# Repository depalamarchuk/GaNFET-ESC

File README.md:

# GaNFET-ESC
This is my master project. Work in progress.

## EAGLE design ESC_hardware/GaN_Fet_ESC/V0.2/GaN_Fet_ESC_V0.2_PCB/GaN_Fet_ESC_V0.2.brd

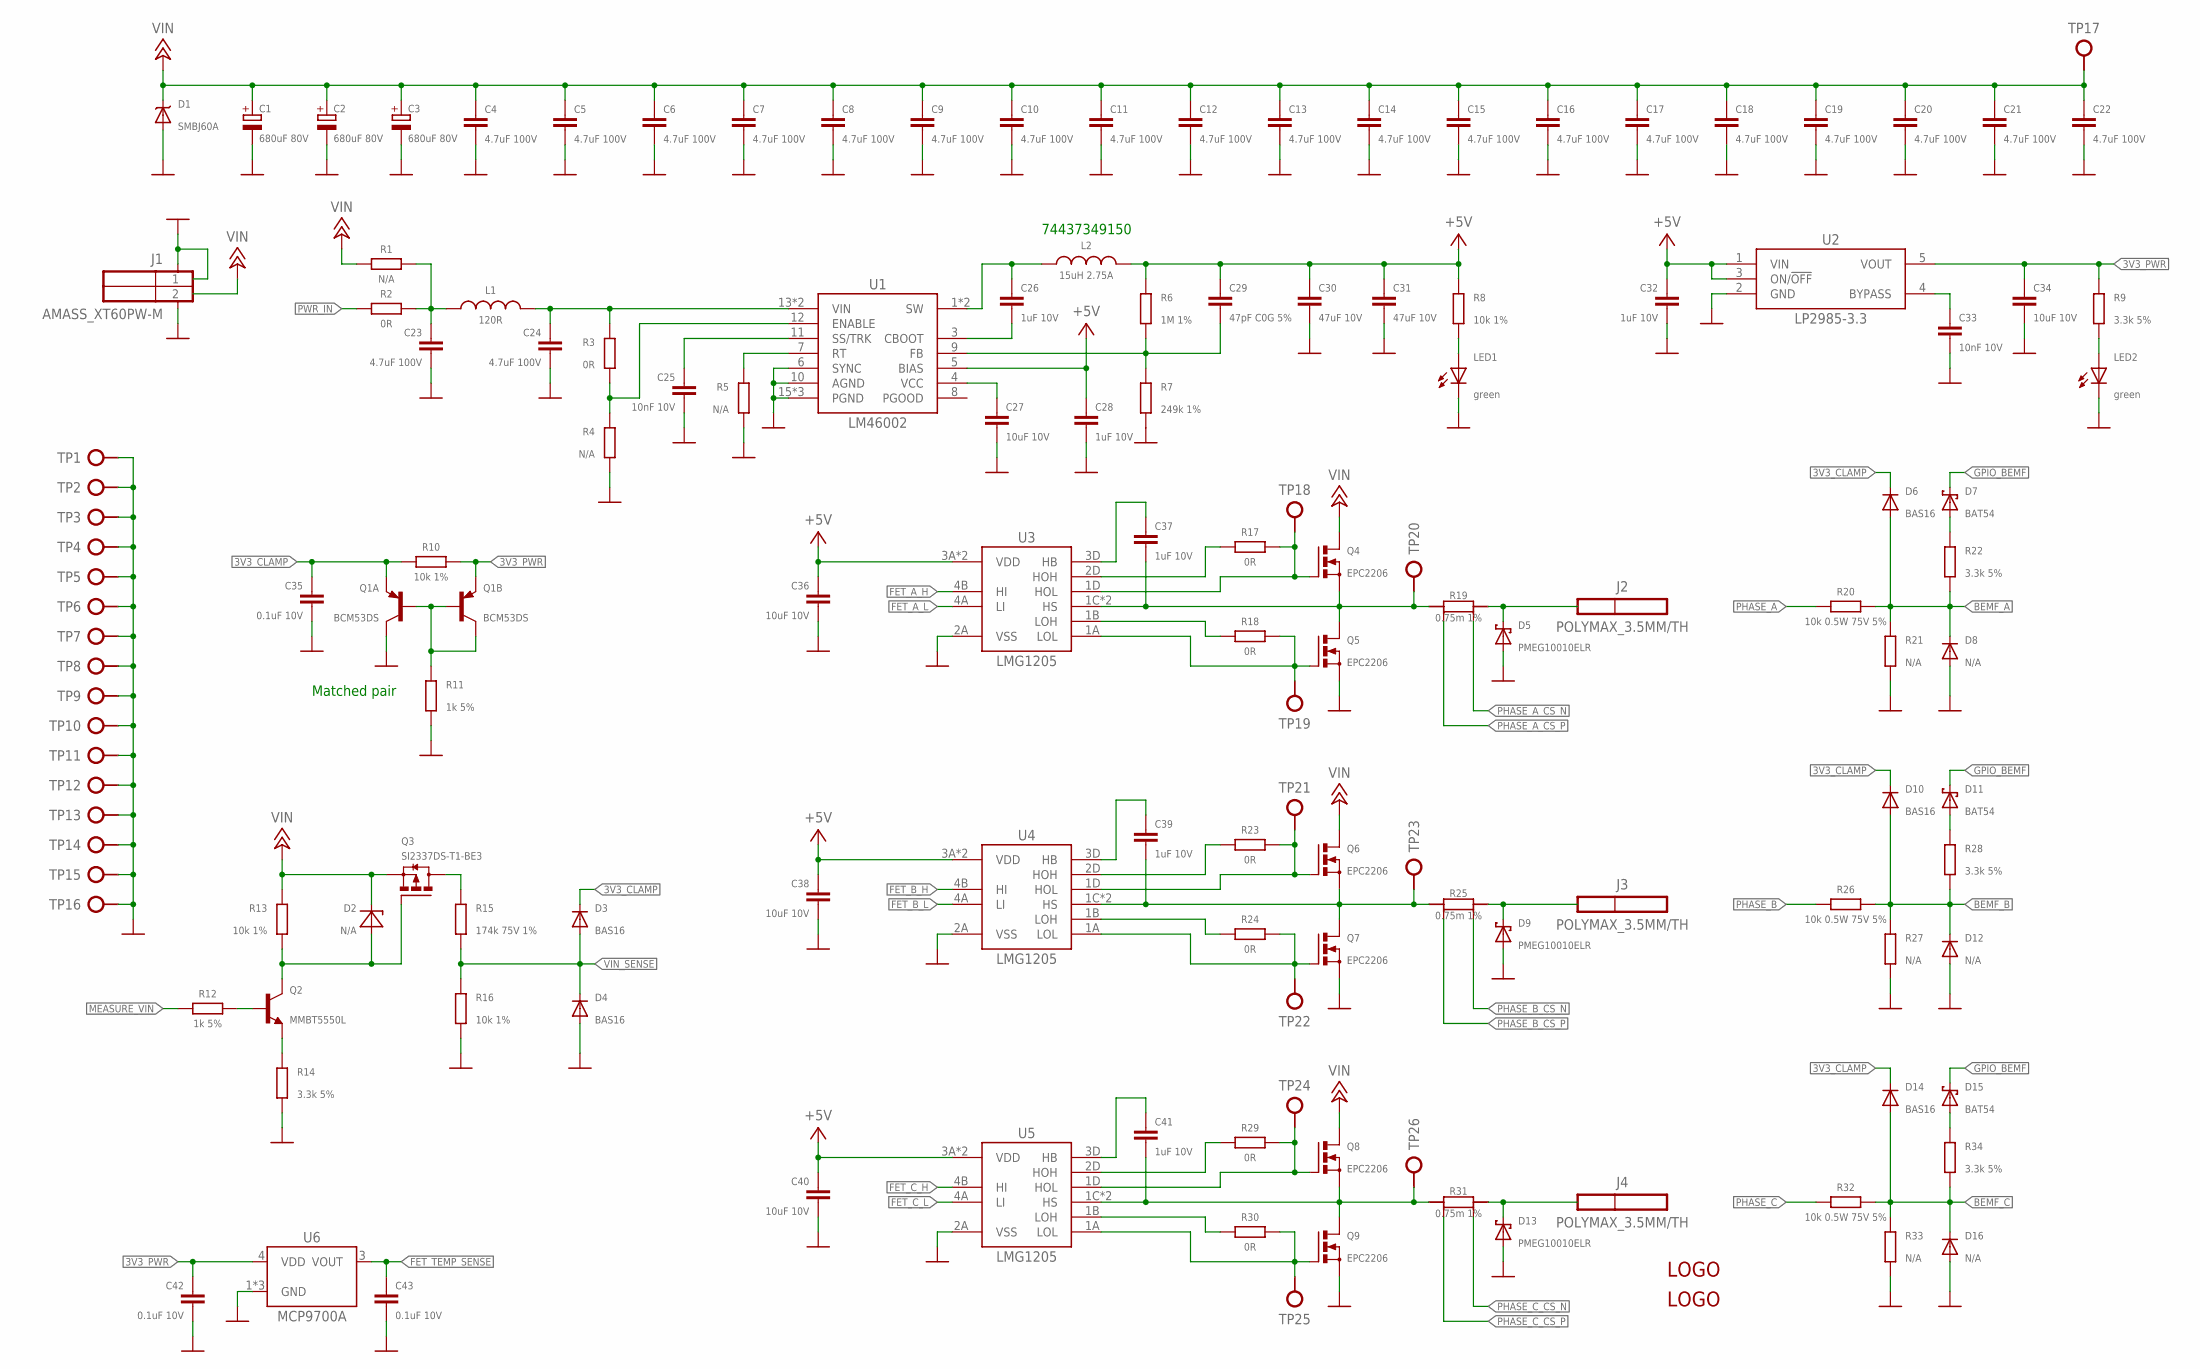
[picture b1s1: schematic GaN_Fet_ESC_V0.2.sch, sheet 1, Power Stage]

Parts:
C1: 680uF 80V; C_7.50_16_26.5_4
C2: 680uF 80V; C_7.50_16_26.5_6
C3: 680uF 80V; C_7.50_16_26.5_5
C4, C5, C6, C7, C8, C9, C10, C11, C12, C13, C14, C15, C16, C17, C18, C19, C20, C21, C22, C23, C24: 4.7uF 100V; C1210
C25, C33: 10nF 10V; C0402
C26, C28, C32, C37, C39, C41: 1uF 10V; C0402
C27, C34, C36, C38, C40: 10uF 10V; C0603
C29: 47pF C0G 5%; C0402
C30, C31: 47uF 10V; C1206
C35, C42, C43: 0.1uF 10V; C0402
D1: SMBJ60A; DO214AA(SMB)
D2: N/A; SOD323F
D3, D4, D6, D10, D14: BAS16; SOD523
D5, D9, D13: PMEG10010ELR; SOD123F
D7, D11, D15: BAT54; SOD523
D8, D12, D16: N/A; SOD523
J1: AMASS_XT60PW-M
J2, J3, J4: POLYMAX_3.5MM/TH; POLYMAX_3.5MM_TH
L1: 120R; L1206
L2: 15uH 2.75A; WURTH_6.6X6.6
LED1, LED2: green; CHIP-LED0603
LOGO1, LOGO2: LOGO
Q1: BCM53DS; SC-74
Q2: MMBT5550L; SOT23
Q3: SI2337DS-T1-BE3; SOT23
Q4, Q5, Q6, Q7, Q8, Q9: EPC2206
R1: N/A; R0603
R2, R3: 0R; R0603
R4, R5, R21, R27, R33: N/A; R0402
R6: 1M 1%; R0402
R7: 249k 1%; R0402
R8, R10, R13, R16: 10k 1%; R0402
R9, R14, R22, R28, R34: 3.3k 5%; R0402
R11, R12: 1k 5%; R0402
R15: 174k 75V 1%; R0603
R17, R18, R23, R24, R29, R30: 0R; R0402
R19, R25, R31: 0.75m 1%; CSS2H-2512
R20, R26, R32: 10k 0.5W 75V 5%; R0805
TP1, TP2, TP3, TP4, TP5, TP6, TP7, TP8, TP9, TP10, TP11, TP12, TP13, TP14, TP15, TP16: TESTPOINT0.5MM; 0.5MM
TP17, TP18, TP19, TP20, TP21, TP22, TP23, TP24, TP25, TP26: TESTPOINT/0.9MM; 0.9MM
U1: LM46002; TSS0P16-PAD
U2: LP2985-3.3; SOT-23-5
U3, U4, U5: LMG1205
U6: MCP9700A; SC-70-5

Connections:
3V3_CLAMP: C35.1, D3.C, D6.C, D10.C, D14.C, Q1.5 (E), R10.1
3V3_PWR: C34.1, C42.1, Q1.4 (E), R9.2, R10.2, U2.5 (VOUT), U6.4 (VDD)
3V3_SINK: Q1.1 (B), Q1.2 (B), Q1.3 (C), R11.2
5V_VCC: C27.1, U1.4 (VCC)
5V_VIN: C24.1, L1.2, R3.2, U1.13 (VIN), U1.14 (VIN)
+5V: C28.1, C29.1, C30.1, C31.1, C32.1, C36.1, C38.1, C40.1, L2.2, R6.2, R8.2, U1.5 (BIAS), U2.1 (VIN), U2.3 (ON/!OFF), U3.3A (VDD), U3.4C (VDD), U4.3A (VDD), U4.4C (VDD), U5.3A (VDD), U5.4C (VDD); also elsewhere on the board
BEMF_A: D6.A, D8.C, R20.2, R21.2, R22.1; also elsewhere on the board
BEMF_B: D10.A, D12.C, R26.2, R27.2, R28.1; also elsewhere on the board
BEMF_C: D14.A, D16.C, R32.2, R33.2, R34.1; also elsewhere on the board
CBOOT: C26.2, U1.3 (CBOOT)
ENABLE: R3.1, R4.2, U1.12 (ENABLE)
FB: C29.2, R6.1, R7.2, U1.9 (FB)
FET_A_H: U3.4B (HI); also elsewhere on the board
FET_A_L: U3.4A (LI); also elsewhere on the board
FET_B_H: U4.4B (HI); also elsewhere on the board
FET_B_L: U4.4A (LI); also elsewhere on the board
FET_C_H: U5.4B (HI); also elsewhere on the board
FET_C_L: U5.4A (LI); also elsewhere on the board
FET_TEMP_SENSE: C43.1, U6.3 (VOUT); also elsewhere on the board
GANFET_A_HB: C37.1, U3.3D (HB)
GANFET_A_HOH: R17.1, U3.2D (HOH)
GANFET_A_HOL: Q4.1 (G), R17.2, TP18.P$1, U3.1D (HOL)
GANFET_A_HS: C37.2, Q4.2 (S), Q4.5 (S), Q4.6 (S), Q4.9 (S), Q4.10 (S), Q4.13 (S), Q4.14 (S), Q4.17 (S), Q4.18 (S), Q4.21 (S), Q4.22 (S), Q4.25 (S), Q4.26 (S), Q4.29 (S), Q4.30 (S), Q5.3 (D), Q5.4 (D), Q5.7 (D), Q5.8 (D), Q5.11 (D), Q5.12 (D), Q5.15 (D), Q5.16 (D), Q5.19 (D), Q5.20 (D), Q5.23 (D), Q5.24 (D), Q5.27 (D), Q5.28 (D), R19.1, R19.3 (1), TP20.P$1, U3.1C (HS), U3.4D (HS)
GANFET_A_LOH: R18.1, U3.1B (LOH)
GANFET_A_LOL: Q5.1 (G), R18.2, TP19.P$1, U3.1A (LOL)
GANFET_B_HB: C39.1, U4.3D (HB)
GANFET_B_HOH: R23.1, U4.2D (HOH)
GANFET_B_HOL: Q6.1 (G), R23.2, TP21.P$1, U4.1D (HOL)
GANFET_B_HS: C39.2, Q6.2 (S), Q6.5 (S), Q6.6 (S), Q6.9 (S), Q6.10 (S), Q6.13 (S), Q6.14 (S), Q6.17 (S), Q6.18 (S), Q6.21 (S), Q6.22 (S), Q6.25 (S), Q6.26 (S), Q6.29 (S), Q6.30 (S), Q7.3 (D), Q7.4 (D), Q7.7 (D), Q7.8 (D), Q7.11 (D), Q7.12 (D), Q7.15 (D), Q7.16 (D), Q7.19 (D), Q7.20 (D), Q7.23 (D), Q7.24 (D), Q7.27 (D), Q7.28 (D), R25.1, R25.3 (1), TP23.P$1, U4.1C (HS), U4.4D (HS)
GANFET_B_LOH: R24.1, U4.1B (LOH)
GANFET_B_LOL: Q7.1 (G), R24.2, TP22.P$1, U4.1A (LOL)
GANFET_C_HB: C41.1, U5.3D (HB)
GANFET_C_HOH: R29.1, U5.2D (HOH)
GANFET_C_HOL: Q8.1 (G), R29.2, TP24.P$1, U5.1D (HOL)
GANFET_C_HS: C41.2, Q8.2 (S), Q8.5 (S), Q8.6 (S), Q8.9 (S), Q8.10 (S), Q8.13 (S), Q8.14 (S), Q8.17 (S), Q8.18 (S), Q8.21 (S), Q8.22 (S), Q8.25 (S), Q8.26 (S), Q8.29 (S), Q8.30 (S), Q9.3 (D), Q9.4 (D), Q9.7 (D), Q9.8 (D), Q9.11 (D), Q9.12 (D), Q9.15 (D), Q9.16 (D), Q9.19 (D), Q9.20 (D), Q9.23 (D), Q9.24 (D), Q9.27 (D), Q9.28 (D), R31.1, R31.3 (1), TP26.P$1, U5.1C (HS), U5.4D (HS)
GANFET_C_LOH: R30.1, U5.1B (LOH)
GANFET_C_LOL: Q9.1 (G), R30.2, TP25.P$1, U5.1A (LOL)
GND: C1.-, C2.-, C3.-, C4.2, C5.2, C6.2, C7.2, C8.2, C9.2, C10.2, C11.2, C12.2, C13.2, C14.2, C15.2, C16.2, C17.2, C18.2, C19.2, C20.2, C21.2, C22.2, C23.2, C24.2, C25.2, C27.2, C28.2, C30.2, C31.2, C32.2, C33.2, C34.2, C35.2, C36.2, C38.2, C40.2, C42.2, C43.2, D1.A, D4.A, D5.A, D8.A, D9.A, D12.A, D13.A, D16.A, J1.1, J1.3, J1.4, LED1.C, LED2.C, Q1.6 (C), Q5.2 (S), Q5.5 (S), Q5.6 (S), Q5.9 (S), Q5.10 (S), Q5.13 (S), Q5.14 (S), Q5.17 (S), Q5.18 (S), Q5.21 (S), Q5.22 (S), Q5.25 (S), Q5.26 (S), Q5.29 (S), Q5.30 (S), Q7.2 (S), Q7.5 (S), Q7.6 (S), Q7.9 (S), Q7.10 (S), Q7.13 (S), Q7.14 (S), Q7.17 (S), Q7.18 (S), Q7.21 (S), Q7.22 (S), Q7.25 (S), Q7.26 (S), Q7.29 (S), Q7.30 (S), Q9.2 (S), Q9.5 (S), Q9.6 (S), Q9.9 (S), Q9.10 (S), Q9.13 (S), Q9.14 (S), Q9.17 (S), Q9.18 (S), Q9.21 (S), Q9.22 (S), Q9.25 (S), Q9.26 (S), Q9.29 (S), Q9.30 (S), R4.1, R5.1, R7.1, R11.1, R14.1, R16.1, R21.1, R27.1, R33.1, TP1.P$1, TP2.P$1, TP3.P$1, TP4.P$1, TP5.P$1, TP6.P$1, TP7.P$1, TP8.P$1, TP9.P$1, TP10.P$1, TP11.P$1, TP12.P$1, TP13.P$1, TP14.P$1, TP15.P$1, TP16.P$1, U1.6 (SYNC), U1.10 (AGND), U1.15 (PGND), U1.16 (PGND), U1.PAD (PGND), U2.2 (GND), U3.2A (VSS), U4.2A (VSS), U5.2A (VSS), U6.1 (GND), U6.2 (GND), U6.5 (GND); also elsewhere on the board
GPIO_BEMF: D7.C, D11.C, D15.C; also elsewhere on the board
LDO_BYPASS: C33.1, U2.4 (BYPASS)
MEASURE_VIN: R12.1; also elsewhere on the board
unnamed: Q2.2 (E), R14.2
unnamed: LED1.A, R8.1
unnamed: D11.A, R28.2
unnamed: D7.A, R22.2
unnamed: D15.A, R34.2
unnamed: LED2.A, R9.1
unnamed: Q2.1 (B), R12.2
unnamed: Q3.3 (D), R15.2
unnamed: C23.1, L1.1, R1.2, R2.2
unnamed: D2.A, Q2.3 (C), Q3.1 (G), R13.1
PHASE_A: D5.C, J2.1, R19.2, R19.4 (2), R20.1
PHASE_A_CS_N: R19.2_SENSE (2K); also elsewhere on the board
PHASE_A_CS_P: R19.1_SENSE (1K); also elsewhere on the board
PHASE_B: D9.C, J3.1, R25.2, R25.4 (2), R26.1
PHASE_B_CS_N: R25.2_SENSE (2K); also elsewhere on the board
PHASE_B_CS_P: R25.1_SENSE (1K); also elsewhere on the board
PHASE_C: D13.C, J4.1, R31.2, R31.4 (2), R32.1
PHASE_C_CS_N: R31.2_SENSE (2K); also elsewhere on the board
PHASE_C_CS_P: R31.1_SENSE (1K); also elsewhere on the board
PWR_IN: R2.1; also elsewhere on the board
RT: R5.2, U1.7 (RT)
SS: C25.1, U1.11 (SS/TRK)
SW: C26.1, L2.1, U1.1 (SW), U1.2 (SW)
VIN: C1.+, C2.+, C3.+, C4.1, C5.1, C6.1, C7.1, C8.1, C9.1, C10.1, C11.1, C12.1, C13.1, C14.1, C15.1, C16.1, C17.1, C18.1, C19.1, C20.1, C21.1, C22.1, D1.K (C), D2.C, J1.2, Q3.2 (S), Q4.3 (D), Q4.4 (D), Q4.7 (D), Q4.8 (D), Q4.11 (D), Q4.12 (D), Q4.15 (D), Q4.16 (D), Q4.19 (D), Q4.20 (D), Q4.23 (D), Q4.24 (D), Q4.27 (D), Q4.28 (D), Q6.3 (D), Q6.4 (D), Q6.7 (D), Q6.8 (D), Q6.11 (D), Q6.12 (D), Q6.15 (D), Q6.16 (D), Q6.19 (D), Q6.20 (D), Q6.23 (D), Q6.24 (D), Q6.27 (D), Q6.28 (D), Q8.3 (D), Q8.4 (D), Q8.7 (D), Q8.8 (D), Q8.11 (D), Q8.12 (D), Q8.15 (D), Q8.16 (D), Q8.19 (D), Q8.20 (D), Q8.23 (D), Q8.24 (D), Q8.27 (D), Q8.28 (D), R1.1, R13.2, TP17.P$1
VIN_SENSE: D3.A, D4.C, R15.1, R16.2; also elsewhere on the board

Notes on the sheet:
74437349150
Matched pair

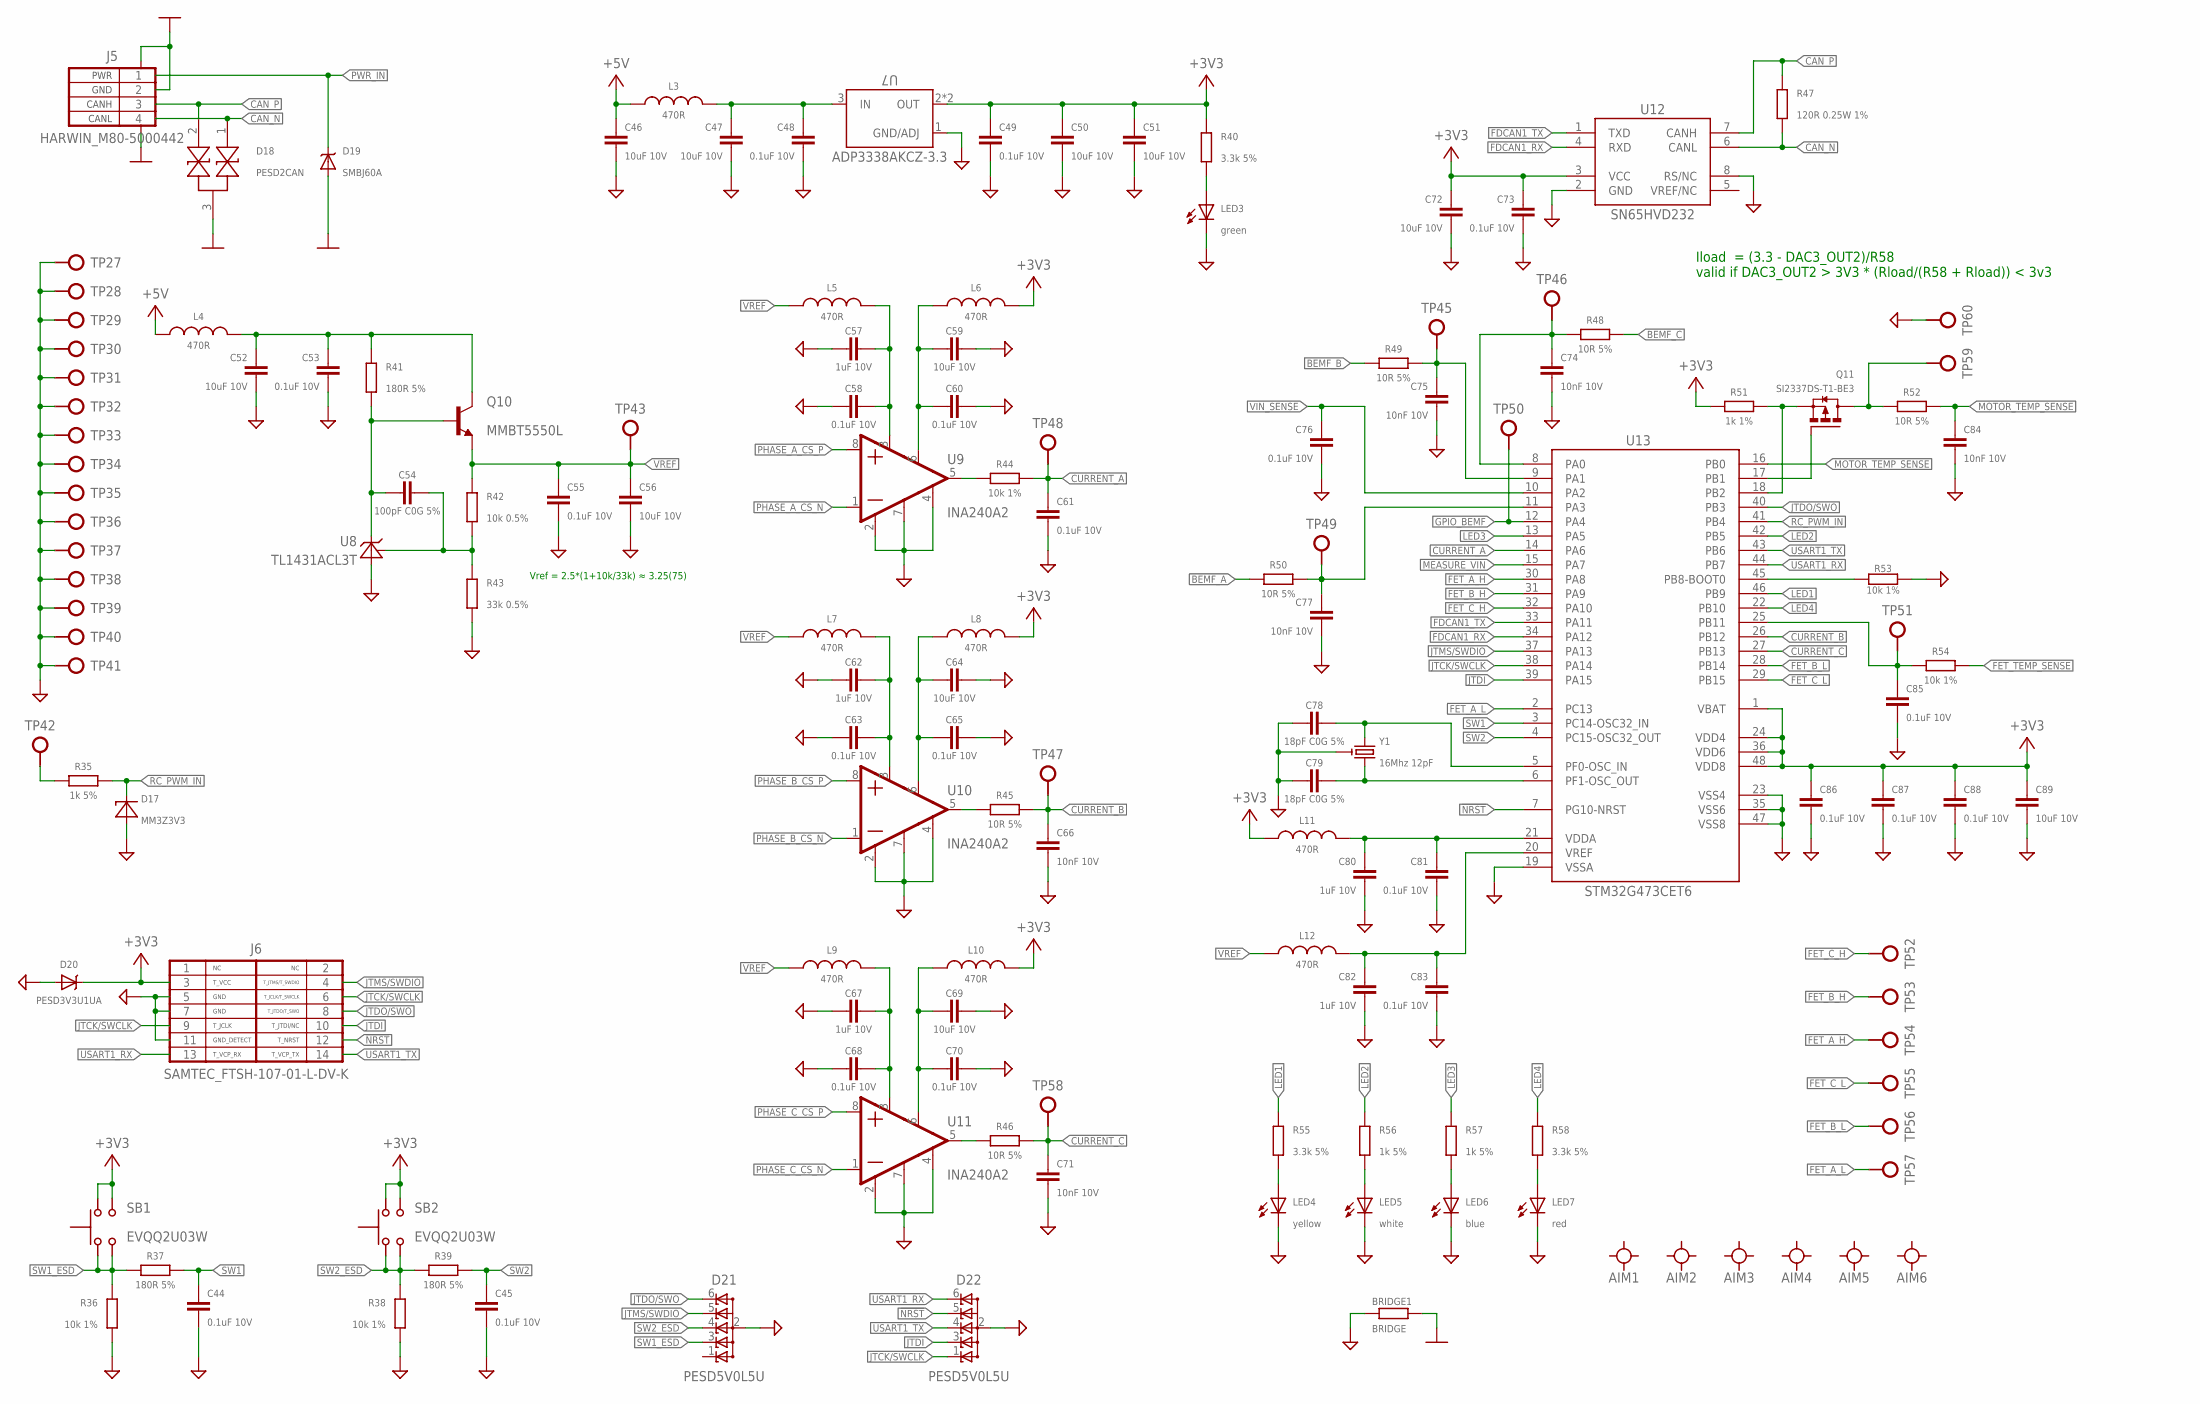
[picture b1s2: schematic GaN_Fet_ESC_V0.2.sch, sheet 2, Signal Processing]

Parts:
AIM1, AIM2, AIM3, AIM4, AIM5, AIM6: AIM_1_MM
BRIDGE1: BRIDGE
C44, C45, C48, C49, C53, C55, C58, C60, C61, C63, C65, C68, C70, C73, C76, C81, C83, C85, C86, C87, C88: 0.1uF 10V; C0402
C46, C47, C50, C51, C52, C56, C59, C64, C69, C72, C89: 10uF 10V; C0603
C54: 100pF C0G 5%; C0402
C57, C62, C67, C80, C82: 1uF 10V; C0402
C66, C71, C74, C75, C77, C84: 10nF 10V; C0402
C78, C79: 18pF C0G 5%; C0402
D17: MM3Z3V3; SOD323F
D18: PESD2CAN; SOT23
D19: SMBJ60A; DO214AA(SMB)
D20: PESD3V3U1UA; SOD323F
D21, D22: PESD5V0L5U; SC-70-6
J5: HARWIN_M80-5000442
J6: SAMTEC_FTSH-107-01-L-DV-K
L3, L4, L5, L6, L7, L8, L9, L10, L11, L12: 470R; L0603
LED3: green; CHIP-LED0603
LED4: yellow; CHIP-LED0603
LED5: white; CHIP-LED0603
LED6: blue; CHIP-LED0603
LED7: red; CHIP-LED0603
Q10: MMBT5550L; SOT23
Q11: SI2337DS-T1-BE3; SOT23
R35, R56, R57: 1k 5%; R0402
R36, R38, R44, R53, R54: 10k 1%; R0402
R37, R39, R41: 180R 5%; R0402
R40, R55, R58: 3.3k 5%; R0402
R42: 10k 0.5%; R0603
R43: 33k 0.5%; R0603
R45, R46, R48, R49, R50, R52: 10R 5%; R0402
R47: 120R 0.25W 1%; R0805
R51: 1k 1%; R0402
SB1, SB2: EVQQ2U03W
TP27, TP28, TP29, TP30, TP31, TP32, TP33, TP34, TP35, TP36, TP37, TP38, TP39, TP40: TESTPOINT0.5MM; 0.5MM
TP41, TP42, TP43, TP45, TP46, TP47, TP48, TP49, TP50, TP51, TP52, TP53, TP54, TP55, TP56, TP57, TP58, TP59, TP60: TESTPOINT/0.9MM; 0.9MM
U7: ADP3338AKCZ-3.3; SOT223
U8: TL1431ACL3T; SOT23
U9, U10, U11: INA240A2; SOIC-8
U12: SN65HVD232; SOIC-8
U13: STM32G473CET6; LQFP-48
Y1: 16Mhz 12pF; CRYSTAL_SMD_3.2X2.5MM

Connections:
!NRST: D22.5, J6.12, U13.7 (PG10-NRST)
+3V3: C49.1, C50.1, C51.1, C72.1, C73.1, C86.1, C87.1, C88.1, C89.1, D20.C, J6.3, L6.1, L8.1, L10.1, L11.1, R40.2, R51.2, SB1.2 (B1), SB1.2' (B2), SB2.2 (B1), SB2.2' (B2), U7.2 (OUT), U7.4 (OUT), U12.3 (VCC), U13.1 (VBAT), U13.24 (VDD4), U13.36 (VDD6), U13.48 (VDD8)
+5V: C46.1, L3.2, L4.2; also elsewhere on the board
BEMF_A: R50.1; also elsewhere on the board
BEMF_A_FILT: C77.1, R50.2, TP49.P$1, U13.11 (PA3)
BEMF_B: R49.1; also elsewhere on the board
BEMF_B_FILT: C75.1, R49.2, TP45.P$1, U13.9 (PA1)
BEMF_C: R48.1; also elsewhere on the board
BEMF_C_FILT: C74.1, R48.2, TP46.P$1, U13.8 (PA0)
BOOT0: R53.2, U13.45 (PB8-BOOT0)
CAN_N: D18.1, J5.4, R47.1, U12.6 (CANL)
CAN_P: D18.2, J5.3, R47.2, U12.7 (CANH)
CS_A: R44.1, U9.5 (OUT)
CS_A_VCC: C59.1, C60.1, L6.2, U9.6 (VS)
CS_B: R45.1, U10.5 (OUT)
CS_B_VCC: C64.1, C65.1, L8.2, U10.6 (VS)
CS_C: R46.2, U11.5 (OUT)
CS_C_VCC: C69.1, C70.1, L10.2, U11.6 (VS)
CURRENT_A: C61.1, R44.2, TP48.P$1, U13.14 (PA6)
CURRENT_B: C66.1, R45.2, TP47.P$1, U13.26 (PB12)
CURRENT_C: C71.1, R46.1, TP58.P$1, U13.27 (PB13)
CURRENT_SOURCE: Q11.3 (D), R52.1, TP59.P$1
FDCAN1_RX: U12.4 (RXD), U13.34 (PA12)
FDCAN1_TX: U12.1 (TXD), U13.33 (PA11)
FET_A_H: TP54.P$1, U13.30 (PA8); also elsewhere on the board
FET_A_L: TP57.P$1, U13.2 (PC13); also elsewhere on the board
FET_B_H: TP53.P$1, U13.31 (PA9); also elsewhere on the board
FET_B_L: TP56.P$1, U13.28 (PB14); also elsewhere on the board
FET_C_H: TP52.P$1, U13.32 (PA10); also elsewhere on the board
FET_C_L: TP55.P$1, U13.29 (PB15); also elsewhere on the board
FET_TEMP_SENSE: R54.1; also elsewhere on the board
FET_TEMP_SENSE_FILT: C85.1, R54.2, TP51.P$1, U13.25 (PB11)
GND: BRIDGE1.2, D18.3, D19.A, J5.2, J5.5, J5.6, J5.7, J5.8; also elsewhere on the board
GND1: BRIDGE1.1, C44.2, C45.2, C46.2, C47.2, C48.2, C49.2, C50.2, C51.2, C52.2, C53.2, C55.2, C56.2, C57.2, C58.2, C59.2, C60.2, C61.2, C62.2, C63.2, C64.2, C65.2, C66.2, C67.2, C68.2, C69.2, C70.2, C71.2, C72.2, C73.2, C74.2, C75.2, C76.2, C77.2, C78.1, C79.1, C80.2, C81.2, C82.2, C83.2, C84.2, C85.2, C86.2, C87.2, C88.2, C89.2, D17.A, D20.A, D21.2, D22.2, J6.5, J6.7, J6.11, LED3.C, LED4.C, LED5.C, LED6.C, LED7.C, R36.1, R38.1, R43.1, R53.1, TP27.P$1, TP28.P$1, TP29.P$1, TP30.P$1, TP31.P$1, TP32.P$1, TP33.P$1, TP34.P$1, TP35.P$1, TP36.P$1, TP37.P$1, TP38.P$1, TP39.P$1, TP40.P$1, TP41.P$1, TP60.P$1, U7.1 (GND/ADJ), U8.3 (A), U9.2 (GND), U9.4 (NC), U9.7 (REF1), U10.2 (GND), U10.4 (NC), U10.7 (REF1), U11.2 (GND), U11.4 (NC), U11.7 (REF1), U12.2 (GND), U12.8 (RS/NC), U13.19 (VSSA), U13.23 (VSS4), U13.35 (VSS6), U13.47 (VSS8), Y1.2 (3), Y1.4 (3)
GPIO_BEMF: TP50.P$1, U13.12 (PA4); also elsewhere on the board
JTCK/SWCLK: D22.1, J6.6, J6.9, U13.38 (PA14)
JTDI: D22.3, J6.10, U13.39 (PA15)
JTDO/SWO: D21.6, J6.8, U13.40 (PB3)
JTMS/SWDIO: D21.5, J6.4, U13.37 (PA13)
LED1: R55.2, U13.46 (PB9)
LED2: R56.2, U13.42 (PB5)
LED3: R57.2, U13.13 (PA5)
LED4: R58.2, U13.22 (PB10)
MCU_VDDA: C80.1, C81.1, L11.2, U13.21 (VDDA)
MCU_VEF: C82.1, C83.1, L12.2, U13.20 (VREF)
MEASURE_VIN: U13.15 (PA7); also elsewhere on the board
MOTOR_TEMP_SENSE: C84.1, R52.2, U13.16 (PB0)
unnamed: LED4.A, R55.1
unnamed: R35.2, TP42.P$1
unnamed: LED3.A, R40.1
unnamed: LED6.A, R57.1
unnamed: LED7.A, R58.1
unnamed: C54.1, Q10.1 (B), R41.1, U8.1 (C)
unnamed: C78.2, U13.5 (PF0-OSC_IN), Y1.1
unnamed: C79.2, U13.6 (PF1-OSC_OUT), Y1.3 (2)
unnamed: C52.1, C53.1, L4.1, Q10.3 (C), R41.2
unnamed: C47.1, C48.1, L3.1, U7.3 (IN)
unnamed: LED5.A, R56.1
OPAMP3_VINM: Q11.2 (S), R51.1, U13.18 (PB2)
OPAMP3_VOUT: Q11.1 (G), U13.17 (PB1)
PHASE_A_CS_N: U9.1 (IN-); also elsewhere on the board
PHASE_A_CS_P: U9.8 (IN+); also elsewhere on the board
PHASE_B_CS_N: U10.1 (IN-); also elsewhere on the board
PHASE_B_CS_P: U10.8 (IN+); also elsewhere on the board
PHASE_C_CS_N: U11.1 (IN-); also elsewhere on the board
PHASE_C_CS_P: U11.8 (IN+); also elsewhere on the board
PWR_IN: D19.K (C), J5.1; also elsewhere on the board
RC_PWM_IN: D17.C, R35.1, U13.41 (PB4)
SW1: C44.1, R37.1, U13.3 (PC14-OSC32_IN)
SW1_ESD: D21.3, R36.2, R37.2, SB1.1 (A1), SB1.1' (A2)
SW2: C45.1, R39.1, U13.4 (PC15-OSC32_OUT)
SW2_ESD: D21.4, R38.2, R39.2, SB2.1 (A1), SB2.1' (A2)
TL431_REF: C54.2, R42.1, R43.2, U8.2 (REF)
USART1_RX: D22.6, J6.13, U13.44 (PB7)
USART1_TX: D22.4, J6.14, U13.43 (PB6)
VIN_SENSE: C76.1, U13.10 (PA2); also elsewhere on the board
VREF: C55.1, C56.1, L5.2, L7.2, L9.2, L12.1, Q10.2 (E), R42.2, TP43.P$1
VREF_A: C57.1, C58.1, L5.1, U9.3 (REF2)
VREF_B: C62.1, C63.1, L7.1, U10.3 (REF2)
VREF_C: C67.1, C68.1, L9.1, U11.3 (REF2)

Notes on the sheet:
T_NRST
GND_DETECT
T_VCC
T_JTMS/T_SWDIO
T_JCLK/T_SWCLK
T_JTDO/T_SWO
GND
T_VCP_TX
T_VCP_RX
T_JCLK
T_JTDI/NC
Vref = 2.5*(1+10k/33k) ≈ 3.25(75)
Iload = (3.3 - DAC3_OUT2)/R58 valid if DAC3_OUT2 > 3V3 * (Rload/(R58 + Rload)) < 3v3
PWR
CANH
CANL

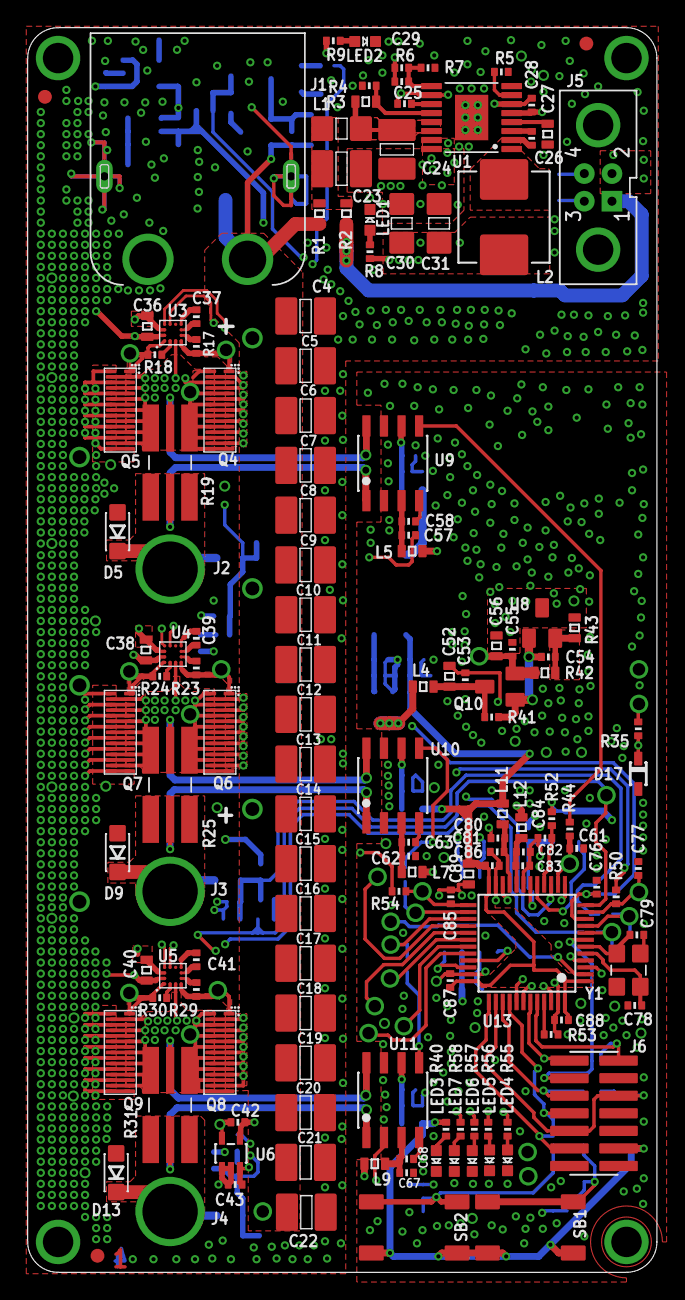
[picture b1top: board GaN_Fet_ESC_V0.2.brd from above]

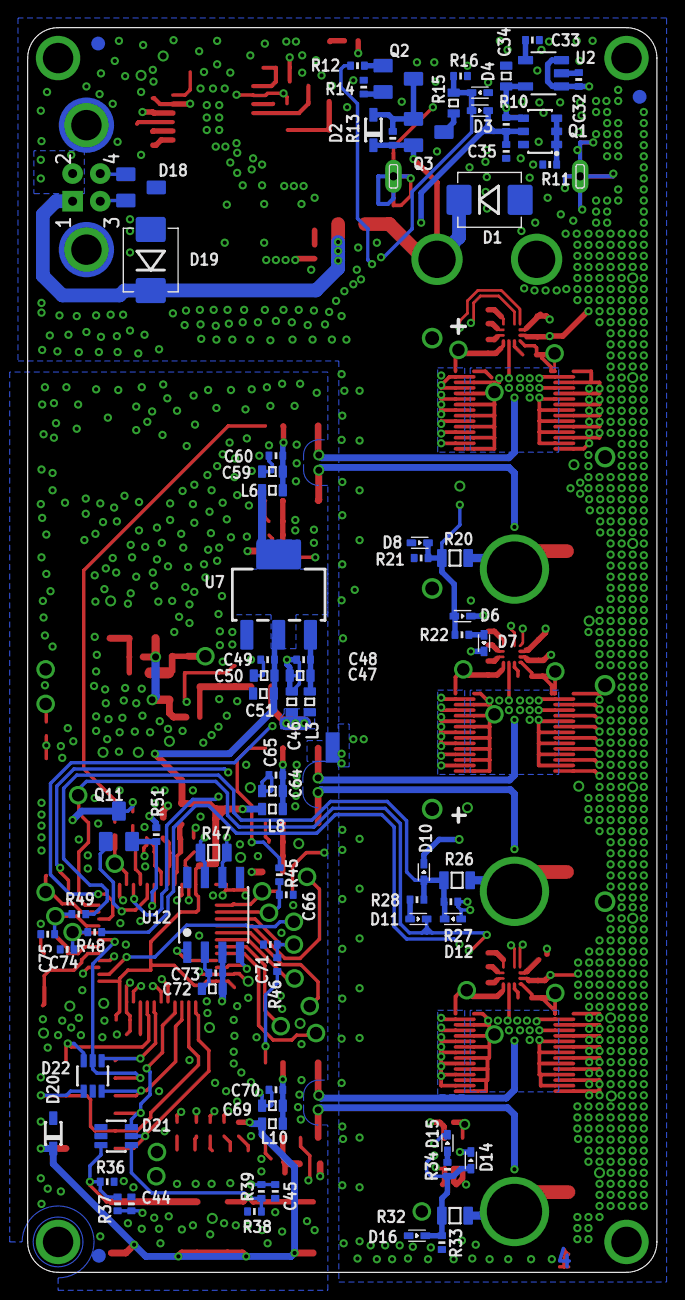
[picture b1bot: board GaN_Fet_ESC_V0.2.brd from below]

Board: 4 copper layers, 45.5 x 90.0 mm, 289 parts (87 on the bottom side), 124 nets.

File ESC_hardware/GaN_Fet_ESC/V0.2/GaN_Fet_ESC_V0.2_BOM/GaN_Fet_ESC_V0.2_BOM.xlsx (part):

|  | GaN Fet Electronic Speed Controller PCB BOM
Qty | Parts | Value | Description | Case | Supplier | Supplier ID | Manufacturer | Manufacturer ID | Alternative manufacturers. 1 – All 2 – First ask 3 – do not replace
2 | C78, C79 | 18pF C0G 5% | ±5% ≥6.3V Ceramic Capacitor C0G/NP0 | C0402 | Mouser | 80-C0402C180J8G | KEMET | C0402C180J8GACTU | 1
1 | C29 | 47pF C0G 5% | ±5% ≥10V Ceramic Capacitor C0G/NP0 | C0402 | Mouser | 80-C0402C470J5G | KEMET | C0402C470J5GACTU | 1
1 | C54 | 100pF C0G 5% | ±5% ≥6.3V Ceramic Capacitor C0G/NP0 | C0402 | Mouser | 80-C0402C101J5G7411 | KEMET | C0402C101J5GAC7411 | 1
8 | C25, C33, C61, C66, C71, C80, C82, C83 | 10nF 10V | ±10% ≥10V Ceramic Capacitor X7R | C0402 | Mouser | 80-C0402C103K3R | KEMET | C0402C103K3RACTU | 1
23 | C35, C42, C43, C44, C45, C48, C49, C53, C55, C58, C60, C63, C65, C68, C70, C73,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 | 0.1uF 10V | ±10% ≥10V Ceramic Capacitor X7R | C0402 | Mouser | 81-GRM155R71H104KE4D | Murata Electronics | GRM155R71H104KE14D | 1
11 | C27, C28, C32, C37, C39, C41, C57, C62, C67, C74, C76 | 1uF 10V | ±10% ≥10V Ceramic Capacitor X7S | C0402 | Mouser | 81-GCM155C71A105KE8D | Murata Electronics | GCM155C71A105KE38D | 1
16 | C26, C34, C36, C38, C40, C46, C47, C50, C51, C52, C56, C59, C64, C69, C72, C87 | 10uF 10V | ±10% ≥10V Ceramic Capacitor X7T | C0603 | Mouser | 81-GRM188D71A106KA3 | Murata Electronics | GRM188D71A106KA73D | 1
21 | C4, C5, C6, C7, C8, C9, C10, C11, C12, C13, C14, C15, C16, C17, C18, C19, C20, 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 | 4.7uF 100V | ±10% ≥100V Ceramic Capacitor X7S | C1210 | Mouser | 963-HMK325C7475KM-PE | Taiyo Yuden | HMK325C7475KM-PE | 1
2 | C30, C31 | 47uF 10V | ±10% ≥10V Ceramic Capacitor X5R | C1206 | Mouser | 81-GRM31CR61A476KE5L | Murata Electronics | GRM31CR61A476KE15L | 1
3 | C1, C2, C3 | 680uF 80V | 680µF 80V Aluminum Electrolytic Capacitors Radial, Can 10000 Hrs @ 105°C | C_7.50_16_26.5 | Mouser | 661-EKZN800E681ML25S | United Chemi-Con | EKZN800ELL681ML25S | 2
6 | R17, R18, R23, R24, R29, R30 | 0R | ±5% 100 mW 50V Chip Resistor 0402 | R0402 | Mouser | 660-RK73Z1ETTP | KOA Speer | RK73Z1ETTP | 1
2 | R2, R3 | 0R | ±5% 100 mW 50V Chip Resistor 0402 | R0603 | Mouser | 667-ERJ-U030R00V | Panasonic | ERJ-U030R00V | 1
3 | R19, R25, R31 | 0.75m 1% | Current Sense Resistors - SMD 3W 0.0007 Ohm 1% | CSS2H-2512 | Mouser | 756-LRMAP25R00075FT4 | Welwyn Components / TT Electronics | LRMAP2512-R00075FT4 | 1
6 | R44, R45, R46, R48, R49, R50 | 10R 5% | ±5% 62.5 mW 50V Chip Resistor 0402 | R0402 | Mouser | 603-RC0402JR-0710RL | YAGEO | RC0402JR-0710RL | 1
1 | R47 | 120R 0.25W 1% | ±1% 250 mW Chip Resistor 0805 | R0805 | Mouser | 667-ERJ-P06F1200V | Panasonic | ERJ-P06F1200V | 1
3 | R37, R39, R41 | 180R 5% | ±5% 62.5 mW 50V Chip Resistor 0402 | R0402 | Mouser | 667-ERJ-2RKF1800X | Panasonic | ERJ-2RKF1800X | 1
5 | R11, R12, R35, R55, R56 | 1k 5% | ±5% 62.5 mW 50V Chip Resistor 0402 | R0402 | Mouser | 603-AC0402JR-071KL | YAGEO | AC0402JR-071KL | 1
9 | R9, R14, R22, R28, R34, R40, R53, R54, R57 | 3.3k 5% | ±5% 62.5 mW 50V Chip Resistor 0402 | R0402 | Mouser | 603-AC0402JR-073K3L | YAGEO | AC0402JR-073K3L | 1
1 | R42 | 10k 0.5% | ±0.5% 25ppm 62.5 mW 50V Chip Resistor 0603 | R0603 | Mouser | 279-CPF0603D10KE | TE Connectivity / Holsworthy | CPF0603D10KE | 1
8 | R8, R10, R13, R16, R36, R38, R51, R52 | 10k 1% | ±1% 62.5 mW 50V Chip Resistor 0402 | R0402 | Mouser | 603-RC0402FR-0710KP | YAGEO | RC0402FR-0710KP | 1
3 | R20, R26, R32 | 10k 0.5W 75V 5% | ±5% 500 mW Chip Resistor 0805 | R0805 | Mouser | 667-ERJ-P06J103V | Panasonic | ERJ-P06J103V | 1
1 | R43 | 33k 0.5% | ±0.5% 25ppm 62.5 mW 50V Chip Resistor 0603 | R0603 | Mouser | 667-ERA-3AED333V | Panasonic | ERA-3AED333V | 1
1 | R15 | 174k 75V 1% | ±1% 62.5 mW 50V Chip Resistor 0603 | R0603 | Mouser | 603-AC0603FR-07174KL | YAGEO | AC0603FR-07174KL | 1
1 | R7 | 249k 1% | ±1% 62.5 mW 50V Chip Resistor 0402, AEC-Q200 | R0402 | Mouser | 660-RK73H1ETTP2493F | KOA Speer | RK73H1ETTP2493F | 1
1 | R6 | 1M 1% | ±1% 62.5 mW 50V Chip Resistor 0402, AEC-Q200 | R0402 | Mouser | 660-RK73H1ETTP1004F | KOA Speer | RK73H1ETTP1004F | 1
1 | L1 | 120R | Ferrite Beads 1206 120ohms ≥3A | L1206 | Mouser | 81-BLM31KN121SZ1L | Murata Electronics | BLM31KN121SZ1L | 1
10 | L3, L4, L5, L6, L7, L8, L9, L10, L11, L12 | 470R | Ferrite Beads 0603 470ohms | L0603 | Mouser | 81-BLM18KG471SN1D | Murata Electronics | BLM18KG471SN1D | 1
1 | L2 | 15uH 2.75A | Fixed Inductors WE-LHMI Powr SMD7050 15uH 2.75A 92mOhm | WURTH_6.6X6.6 | Mouser | 710-74437349150 | Wurth Elektronik | 74437349150 | 3
1 | Y1 | 16Mhz 12pF | Crystals AEC-Q200 16MHz 12pF 3.2x2.5mm | CRYSTAL_SMD_3.2X2.5MM | Mouser | 581-CX3225SB16000HLJ | Kyocera AVX | CX3225SB16000H0FLJCC | 1
2 | D1, D21 | SMBJ60A | ESD Suppressors / TVS Diodes 60volts 5uA 6.2 Amps Uni-Dir | DO214AA(SMB) | Mouser | 652-SMBJ60A | Bourns | SMBJ60A | 1
1 | D2 | MM3Z12V | Zener Diodes 12V 200mW | SOD323F | Mouser | 863-MM3Z12VT1G | onsemi | MM3Z12VT1G | 1
5 | D3, D4, D7, D12, D17 | BAS16 | Diodes - General Purpose, Power, Switching SWITCHING DIODE | SOD523 | Mouser | 863-BAS16XV2T5G | onsemi | BAS16XV2T5G | 1
3 | D5, D10, D15 | PMEG10010ELR | Schottky Diodes & Rectifiers 1A Schottky Barrier Rectifier | SOD123F | Mouser | 771-PMEG10010ELRX | Nexperia | PMEG10010ELRX | 1
3 | D8, D13, D18 | BAT54 | Schottky Diodes & Rectifiers 30V 200mW Single | SOD523 | Mouser | 863-BAT54XV2T1G | onsemi | BAT54XV2T1G | 1
1 | D20 | PESD2CAN | ESD Suppressors / TVS Diodes DIODE ESD PROT | SOT23 | Mouser | 771-PESD2CANFD24V-TR | Nexperia | PESD2CANFD24V-TR | 1
1 | D22 | MM3Z3V3 | Zener Diodes 3.3V 200mW | SOD323F | Mouser | 863-MM3Z3V3T1G | onsemi | MM3Z3V3T1G | 1
1 | D23 | PESD3V3U1UA | ESD Suppressors / TVS Diodes DIODE ARRAY ESD 1L ULTRA LO CD | SOD323F | Mouser | 771-PESD3V3U1UA-T/R | Nexperia | PESD3V3U1UA,115 | 1
2 | D24, D25 | PESD5V0L5U | ESD Suppressors / TVS Diodes Diode TVS Quint Uni-Dir 5V 25W 6-Pin | SC-70-6 | Mouser | 771-PESD5V0L5UY,125 | Nexperia | PESD5V0L5UY,125 | 1
4 | LED1, LED2, LED3, LED4 | green | Green 570nm LED Indication - Discrete 2V 0603 (1608 Metric) | CHIP-LED0603 | Mouser | 710-150060VS75000 | Wurth Elektronik | 150060VS75000 | 1
1 | LED5 | yellow | Yellow 589nm LED Indication - Discrete 2V 0603 (1608 Metric) | CHIP-LED0603 | Mouser | 710-150060YS75000 | Wurth Elektronik | 150060YS75000 | 1
1 | LED6 | white | Standard LEDs - SMD White Clear Non-Diff | CHIP-LED0603 | Mouser | 78-VLMW1300-GS08 | Vishay Semiconductors | VLMW1300-GS08 | 1
1 | LED7 | blue | Blue 470nm LED Indication - Discrete 3.2V 0603 (1608 Metric) | CHIP-LED0603 | Mouser | 710-150060BS75000 | Wurth Elektronik | 150060BS75000 | 1
1 | LED8 | red | Red 625nm LED Indication - Discrete 2V 0603 (1608 Metric) | CHIP-LED0603 | Mouser | 710-150060RS75000 | Wurth Elektronik | 150060RS75000 | 1
1 | Q1 | BCM53DS | Bipolar Transistors - BJT BCM53DS SC-74 | SC-74 | Mouser | 771-BCM53DSX | Nexperia | BCM53DSX | 2
2 | Q2, Q10 | MMBT5550L | Bipolar Transistors - BJT SS HV XSTR NPN 160V | SOT23 | Mouser | 863-MMBT5550LT1G | onsemi | MMBT5550LT1G | 1
1 | Q3 | SI2337DS-T1-BE3 | MOSFET P-CHANNEL 80-V (D-S) | SOT23C | Mouser | SI2337DS-T1-BE3 | Vishay / Siliconix | SI2337DS-T1-BE3 | 1
6 | Q4, Q5, Q6, Q7, Q8, Q9 | EPC2206 | GaN FET, eGaN®, Vds = 80V, Rds(on) = 2.2 mOhm, Id = 90 A, Qgd = 3 nC, Qrr = 0 n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 | EPC2206 | Digi-Key | 917-1212-1-ND | EPC | EPC2206 | 2
1 | U1 | LM46002 | 3.5-V to 60-V, 2-A Synchronous Step-Down Voltage Converter | TSS0P16-PAD | Mouser | 595-LM46002PWPR | Texas Instruments | LM46002PWPR | 3
1 | U2 | LP2985-3.3 | LP2985 150-mA Low-noise Low-dropout Regulator With Shutdown | SOT-23-5 | Mouser | 595-LP2985-33DBVR | Texas Instruments | LP2985-33DBVR | 2
3 | U3, U4, U5 | LMG1205 | LMG120580-V, 1.2-A to 5-A, Half Bridge GaN Driver with Integrated Bootstrap Dio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 | LMG1205 | Mouser | 595-LMG1205YFXR | Texas Instruments | LMG1205YFXR | 3
1 | U6 | MCP9700A | Temperature Sensor Analog, Local -40°C ~ 125°C 10mV/°C SC-70-5 | SC-70-5 | Mouser | 579-MCP9700AT-E/LT | Microchip Technology | MCP9700AT-E/LT | 3
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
